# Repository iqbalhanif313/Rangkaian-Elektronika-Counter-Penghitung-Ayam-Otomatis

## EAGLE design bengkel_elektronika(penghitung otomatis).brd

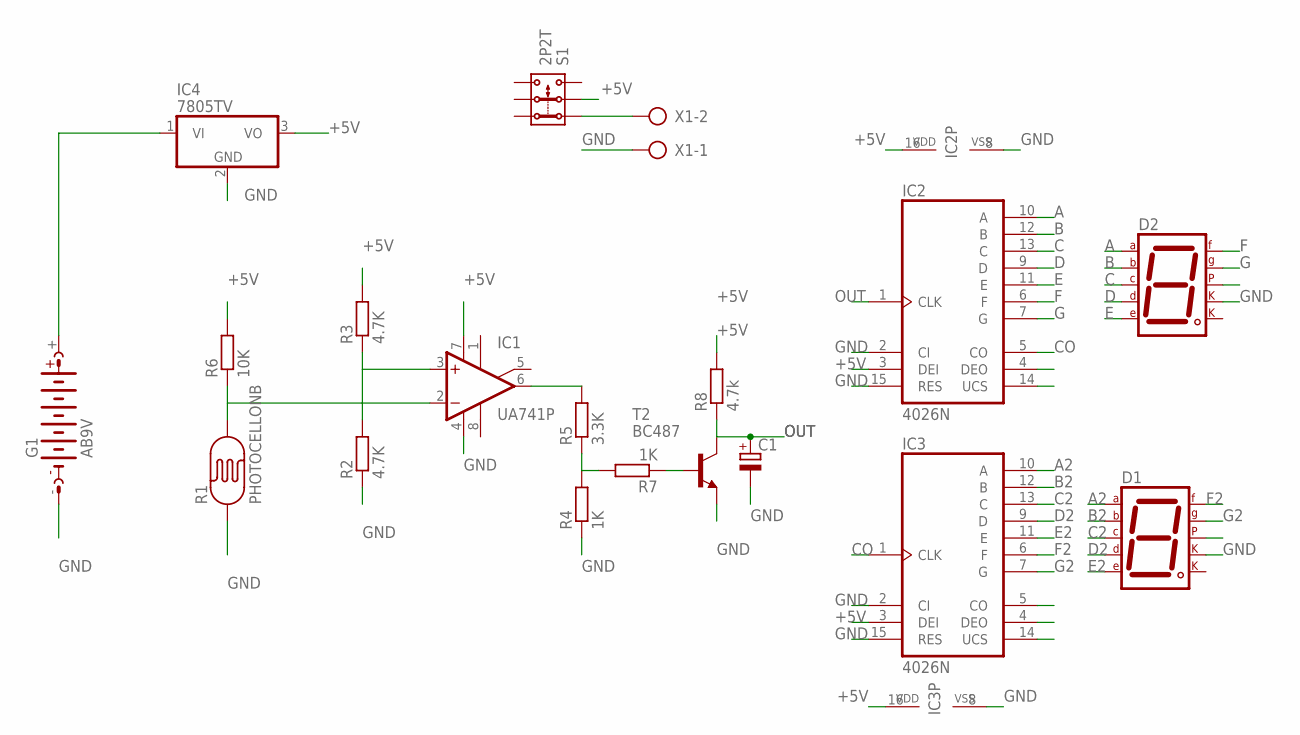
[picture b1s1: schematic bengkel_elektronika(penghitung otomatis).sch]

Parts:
C1: CPOL-EUE2-4; E2-4
D1, D2: 7SEG-CK; 7SEG-13
G1: AB9V
IC1: UA741P; DIL08
IC2, IC3: 4026N; DIL16
IC4: 7805TV; TO220V
R1: PHOTOCELLONB; ON_BOARD
R2, R3: 4.7K; 0207/7
R4, R7: 1K; 0207/7
R5: 3.3K; 0207/7
R6: 10K; 0207/7
R8: 4.7k; 0207/7
S1: 2P2T
T2: BC487; TO92-EBC
X1: AK500/2

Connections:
+5V: IC1.7 (V+), IC2.3 (DEI), IC2.16 (VDD), IC3.3 (DEI), IC3.16 (VDD), IC4.3 (VO), R3.2, R6.2, R8.2, S1.2.1
A: D2.7 (A), IC2.10 (A)
A2: D1.7 (A), IC3.10 (A)
B: D2.6 (B), IC2.12 (B)
B2: D1.6 (B), IC3.12 (B)
C: D2.4 (C), IC2.13 (C)
C2: D1.4 (C), IC3.13 (C)
CO: IC2.5 (CO), IC3.1 (CLK)
D: D2.2 (D), IC2.9 (D)
D2: D1.2 (D), IC3.9 (D)
E: D2.1 (E), IC2.11 (E)
E2: D1.1 (E), IC3.11 (E)
F: D2.9 (F), IC2.6 (F)
F2: D1.9 (F), IC3.6 (F)
G: D2.10 (G), IC2.7 (G)
G2: D1.10 (G), IC3.7 (G)
GND: C1.-, D1.3 (CK1), D2.3 (CK1), G1.-, IC1.4 (V-), IC2.2 (CI), IC2.8 (VSS), IC2.15 (RES), IC3.2 (CI), IC3.8 (VSS), IC3.15 (RES), IC4.2 (GND), R1.1, R2.1, R4.1, T2.E, X1.1
unnamed: IC1.2 (-IN), R1.2, R6.1
unnamed: IC1.3 (+IN), R2.2, R3.1
unnamed: IC1.6 (OUT), R5.2
unnamed: R4.2, R5.1, R7.2
unnamed: R7.1, T2.B
unnamed: S1.1.1, X1.2
unnamed: G1.+, IC4.1 (VI)
OUT: C1.+, IC2.1 (CLK), R8.1, T2.C

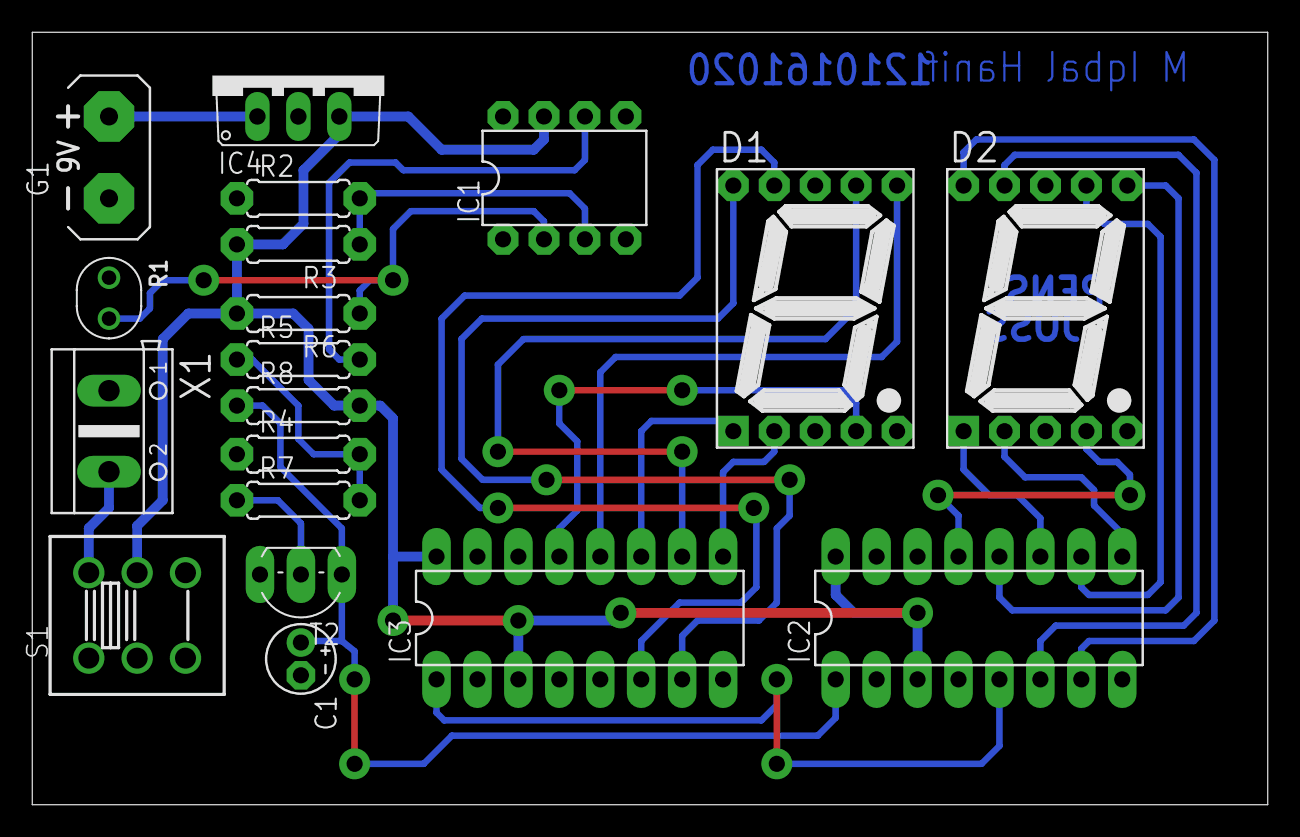
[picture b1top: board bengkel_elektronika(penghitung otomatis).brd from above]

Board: 2 copper layers, 76.7 x 47.9 mm, 19 parts (0 on the bottom side), 25 nets.
